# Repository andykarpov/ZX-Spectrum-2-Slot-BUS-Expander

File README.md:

# ZX-Spectrum-2Slot-BUS-Expander

Modified original version with Nemo Bus slot.

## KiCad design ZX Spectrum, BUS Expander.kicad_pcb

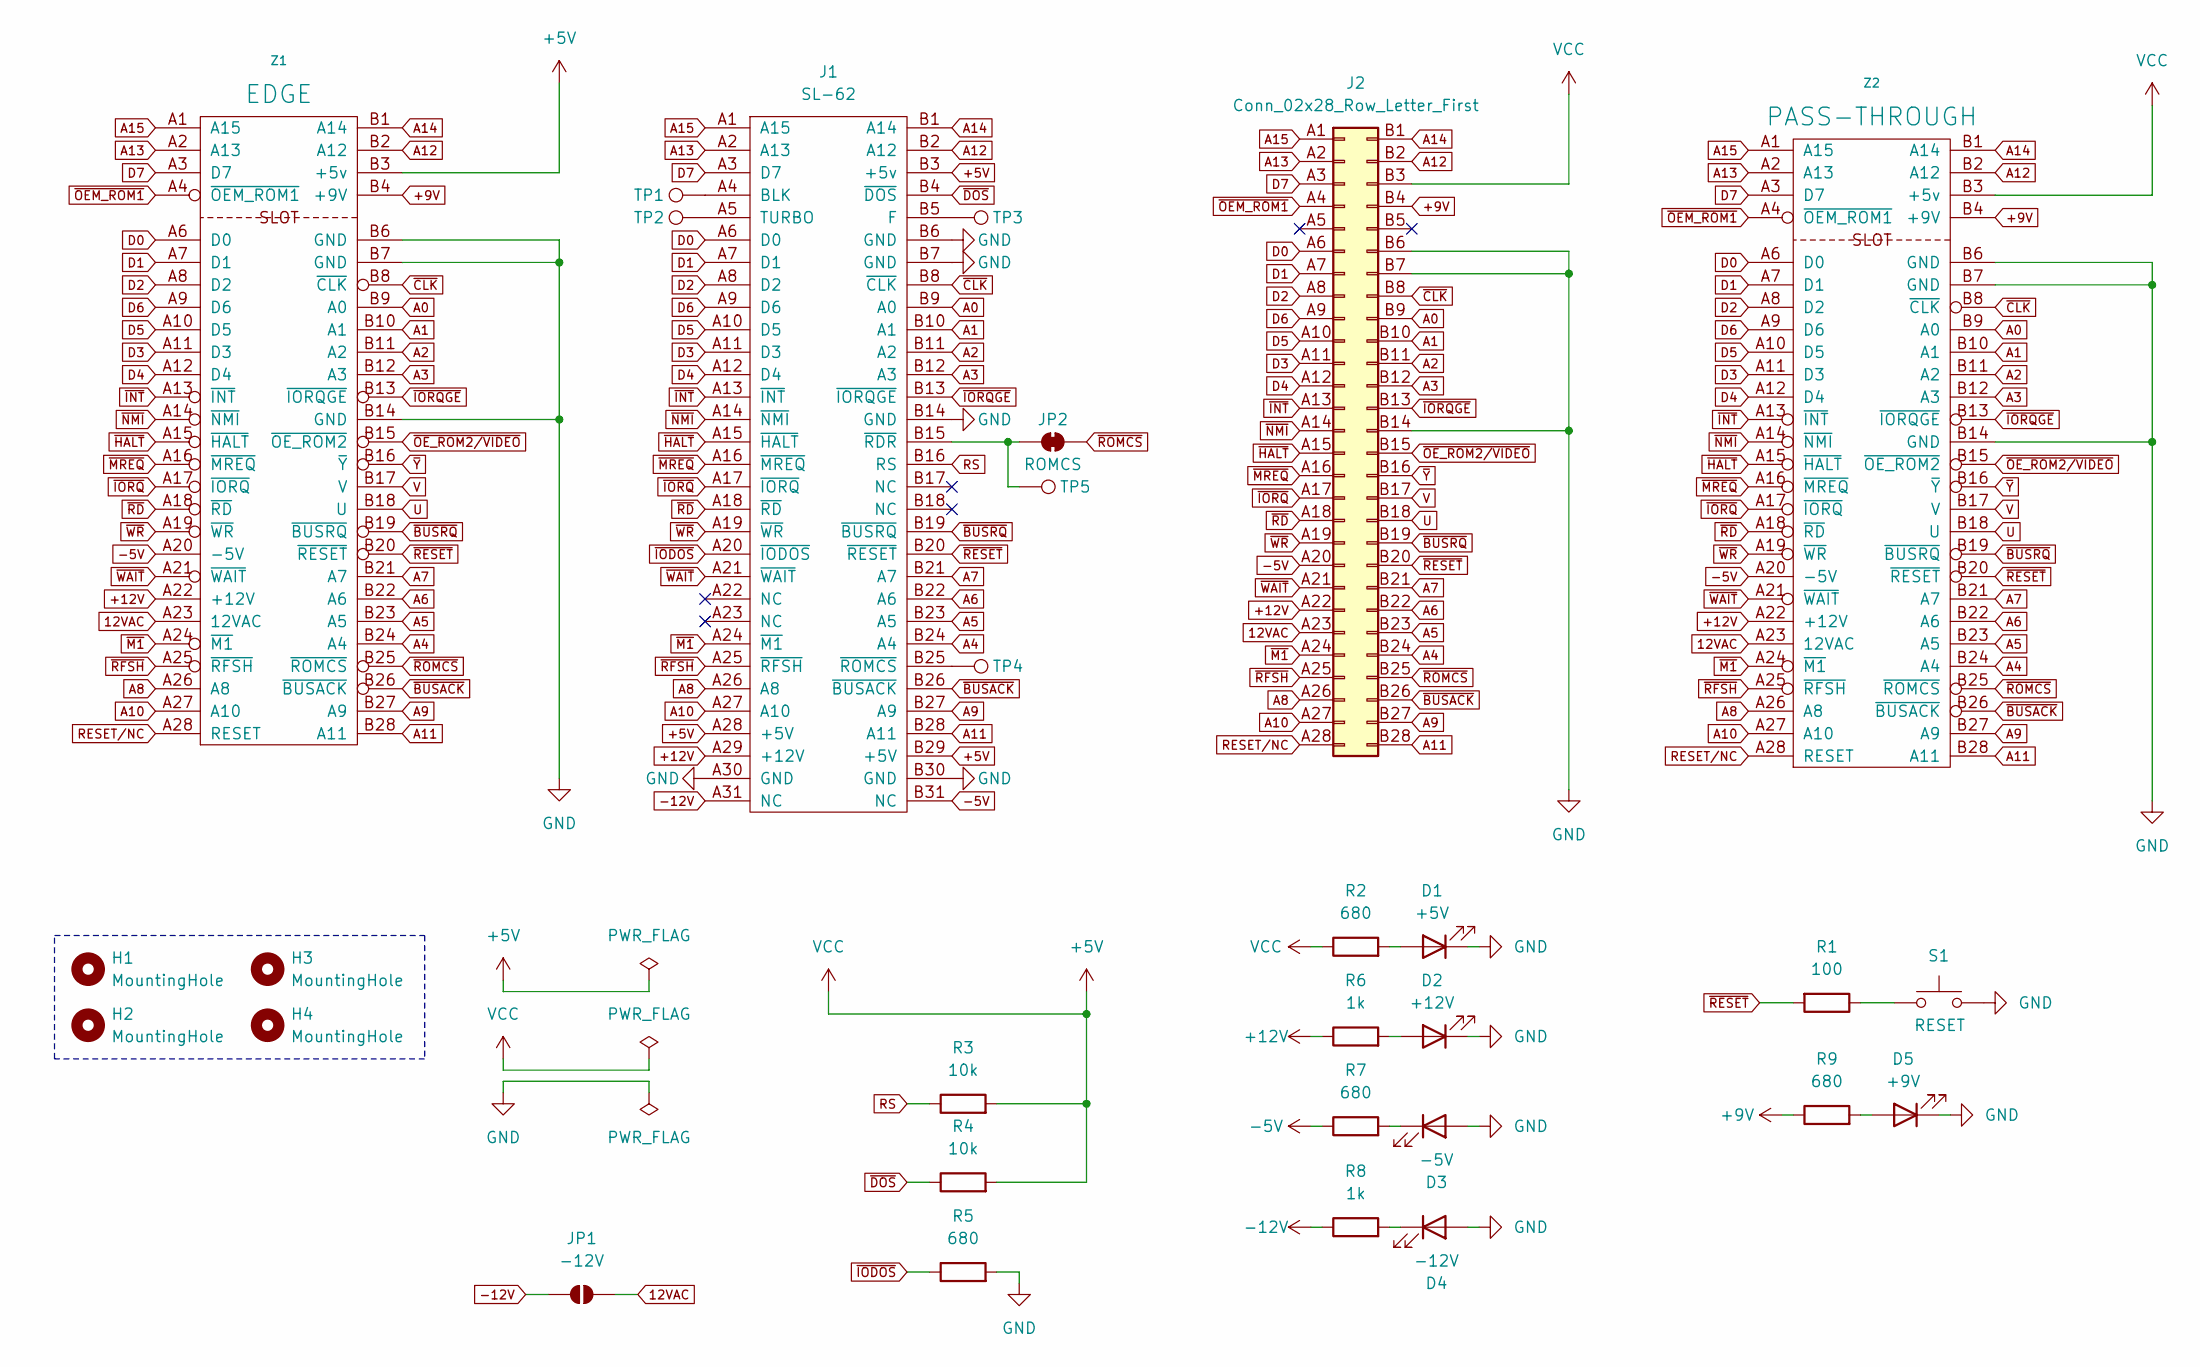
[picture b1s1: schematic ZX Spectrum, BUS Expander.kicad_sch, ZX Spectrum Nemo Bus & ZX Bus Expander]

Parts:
D1: +5V; LED_0805_2012Metric_Pad1.15x1.40mm_HandSolder
D2: +12V; LED_0805_2012Metric_Pad1.15x1.40mm_HandSolder
D3: -5V; LED_0805_2012Metric_Pad1.15x1.40mm_HandSolder
D4: -12V; LED_0805_2012Metric_Pad1.15x1.40mm_HandSolder
D5: +9V; LED_0805_2012Metric_Pad1.15x1.40mm_HandSolder
H1, H2, H3, H4: MountingHole; MountingHole_3.2mm_M3
J1: SL-62; NemoBus-SL62-inverted
J2: Conn_02x28_Row_Letter_First; ZX Bus Socket
JP1: -12V; SolderJumper-2_P1.3mm_Open_RoundedPad1.0x1.5mm
JP2: ROMCS; SolderJumper-2_P1.3mm_Bridged_RoundedPad1.0x1.5mm
R1: 100; R_0805_2012Metric_Pad1.20x1.40mm_HandSolder
R2, R5, R7, R9: 680; R_0805_2012Metric_Pad1.20x1.40mm_HandSolder
R3, R4: 10k; R_0805_2012Metric_Pad1.20x1.40mm_HandSolder
R6, R8: 1k; R_0805_2012Metric_Pad1.20x1.40mm_HandSolder
S1: RESET; SW_PUSH_6mm; Mouser Part Number 611-PTS526SM15SMTR2L
TP1, TP2, TP3, TP4, TP5: TestPoint; TestPoint_Pad_D2.0mm
Z1: EDGE; ZX Bus, Edge
Z2: PASS-THROUGH; ZX Bus, Edge Pass-T

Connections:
12VAC: J2.A23 (Pin_a23), JP1.2 (B), Z1.A23 (12VAC), Z2.A23 (12VAC)
+5V: J1.A28 (+5V), J1.B3 (+5v), J1.B29 (+5V), J2.B3 (Pin_b3), R2.1, R3.2, R4.2, Z1.B3 (+5v), Z2.B3 (+5v)
+9V: J2.B4 (Pin_b4), R9.1, Z1.B4 (+9V), Z2.B4 (+9V)
+12V: J1.A29 (+12V), J2.A22 (Pin_a22), R6.1, Z1.A22 (+12V), Z2.A22 (+12V)
-5V: J1.B31 (NC), J2.A20 (Pin_a20), R7.1, Z1.A20 (-5V), Z2.A20 (-5V)
-12V: J1.A31 (NC), JP1.1 (A), R8.1
A0: J1.B9 (A0), J2.B9 (Pin_b9), Z1.B9 (A0), Z2.B9 (A0)
A1: J1.B10 (A1), J2.B10 (Pin_b10), Z1.B10 (A1), Z2.B10 (A1)
A2: J1.B11 (A2), J2.B11 (Pin_b11), Z1.B11 (A2), Z2.B11 (A2)
A3: J1.B12 (A3), J2.B12 (Pin_b12), Z1.B12 (A3), Z2.B12 (A3)
A4: J1.B24 (A4), J2.B24 (Pin_b24), Z1.B24 (A4), Z2.B24 (A4)
A5: J1.B23 (A5), J2.B23 (Pin_b23), Z1.B23 (A5), Z2.B23 (A5)
A6: J1.B22 (A6), J2.B22 (Pin_b22), Z1.B22 (A6), Z2.B22 (A6)
A7: J1.B21 (A7), J2.B21 (Pin_b21), Z1.B21 (A7), Z2.B21 (A7)
A8: J1.A26 (A8), J2.A26 (Pin_a26), Z1.A26 (A8), Z2.A26 (A8)
A9: J1.B27 (A9), J2.B27 (Pin_b27), Z1.B27 (A9), Z2.B27 (A9)
A10: J1.A27 (A10), J2.A27 (Pin_a27), Z1.A27 (A10), Z2.A27 (A10)
A11: J1.B28 (A11), J2.B28 (Pin_b28), Z1.B28 (A11), Z2.B28 (A11)
A12: J1.B2 (A12), J2.B2 (Pin_b2), Z1.B2 (A12), Z2.B2 (A12)
A13: J1.A2 (A13), J2.A2 (Pin_a2), Z1.A2 (A13), Z2.A2 (A13)
A14: J1.B1 (A14), J2.B1 (Pin_b1), Z1.B1 (A14), Z2.B1 (A14)
A15: J1.A1 (A15), J2.A1 (Pin_a1), Z1.A1 (A15), Z2.A1 (A15)
D0: J1.A6 (D0), J2.A6 (Pin_a6), Z1.A6 (D0), Z2.A6 (D0)
D1: J1.A7 (D1), J2.A7 (Pin_a7), Z1.A7 (D1), Z2.A7 (D1)
D2: J1.A8 (D2), J2.A8 (Pin_a8), Z1.A8 (D2), Z2.A8 (D2)
D3: J1.A11 (D3), J2.A11 (Pin_a11), Z1.A11 (D3), Z2.A11 (D3)
D4: J1.A12 (D4), J2.A12 (Pin_a12), Z1.A12 (D4), Z2.A12 (D4)
D5: J1.A10 (D5), J2.A10 (Pin_a10), Z1.A10 (D5), Z2.A10 (D5)
D6: J1.A9 (D6), J2.A9 (Pin_a9), Z1.A9 (D6), Z2.A9 (D6)
D7: J1.A3 (D7), J2.A3 (Pin_a3), Z1.A3 (D7), Z2.A3 (D7)
GND: D1.1 (K), D2.1 (K), D3.2 (A), D4.2 (A), D5.1 (K), J1.A30 (GND), J1.B6 (GND), J1.B7 (GND), J1.B14 (GND), J1.B30 (GND), J2.B6 (Pin_b6), J2.B7 (Pin_b7), J2.B14 (Pin_b14), R5.2, S1.2, Z1.B6 (GND), Z1.B7 (GND), Z1.B14 (GND), Z2.B6 (GND), Z2.B7 (GND), Z2.B14 (GND)
unnamed: D1.2 (A), R2.2
unnamed: D2.2 (A), R6.2
unnamed: D3.1 (K), R7.2
unnamed: D4.1 (K), R8.2
unnamed: D5.2 (A), R9.2
unnamed: J1.A4 (BLK), TP1.1
unnamed: J1.B5 (F), TP3.1
unnamed: J1.A5 (TURBO), TP2.1
unnamed: J1.B15 (~RDR), JP2.1 (A), TP5.1
unnamed: J1.B25 (~ROMCS), TP4.1
unnamed: R1.1, S1.1
RESET/NC: J2.A28 (Pin_a28), Z1.A28 (RESET), Z2.A28 (RESET)
RS: J1.B16 (RS), R3.1
U: J2.B18 (Pin_b18), Z1.B18 (U), Z2.B18 (U)
V: J2.B17 (Pin_b17), Z1.B17 (V), Z2.B17 (V)
~BUSACK: J1.B26 (~BUSACK), J2.B26 (Pin_b26), Z1.B26 (~BUSACK), Z2.B26 (~BUSACK)
~BUSRQ: J1.B19 (~BUSRQ), J2.B19 (Pin_b19), Z1.B19 (~BUSRQ), Z2.B19 (~BUSRQ)
~CLK: J1.B8 (~CLK), J2.B8 (Pin_b8), Z1.B8 (~CLK), Z2.B8 (~CLK)
~DOS: J1.B4 (~DOS), R4.1
~HALT: J1.A15 (~HALT), J2.A15 (Pin_a15), Z1.A15 (~HALT), Z2.A15 (~HALT)
~INT: J1.A13 (~INT), J2.A13 (Pin_a13), Z1.A13 (~INT), Z2.A13 (~INT)
~IODOS: J1.A20 (~IODOS), R5.1
~IORQGE: J1.B13 (~IORQGE), J2.B13 (Pin_b13), Z1.B13 (~IORQGE), Z2.B13 (~IORQGE)
~IORQ: J1.A17 (~IORQ), J2.A17 (Pin_a17), Z1.A17 (~IORQ), Z2.A17 (~IORQ)
~M1: J1.A24 (~M1), J2.A24 (Pin_a24), Z1.A24 (~M1), Z2.A24 (~M1)
~MREQ: J1.A16 (~MREQ), J2.A16 (Pin_a16), Z1.A16 (~MREQ), Z2.A16 (~MREQ)
~NMI: J1.A14 (~NMI), J2.A14 (Pin_a14), Z1.A14 (~NMI), Z2.A14 (~NMI)
~OEM_ROM1: J2.A4 (Pin_a4), Z1.A4 (~OEM_ROM1), Z2.A4 (~OEM_ROM1)
~OE_ROM2/VIDEO: J2.B15 (Pin_b15), Z1.B15 (~OE_ROM2), Z2.B15 (~OE_ROM2)
~RD: J1.A18 (~RD), J2.A18 (Pin_a18), Z1.A18 (~RD), Z2.A18 (~RD)
~RESET: J1.B20 (~RESET), J2.B20 (Pin_b20), R1.2, Z1.B20 (~RESET), Z2.B20 (~RESET)
~RFSH: J1.A25 (~RFSH), J2.A25 (Pin_a25), Z1.A25 (~RFSH), Z2.A25 (~RFSH)
~ROMCS: J2.B25 (Pin_b25), JP2.2 (B), Z1.B25 (~ROMCS), Z2.B25 (~ROMCS)
~WAIT: J1.A21 (~WAIT), J2.A21 (Pin_a21), Z1.A21 (~WAIT), Z2.A21 (~WAIT)
~WR: J1.A19 (~WR), J2.A19 (Pin_a19), Z1.A19 (~WR), Z2.A19 (~WR)
~Y: J2.B16 (Pin_b16), Z1.B16 (~Y), Z2.B16 (~Y)

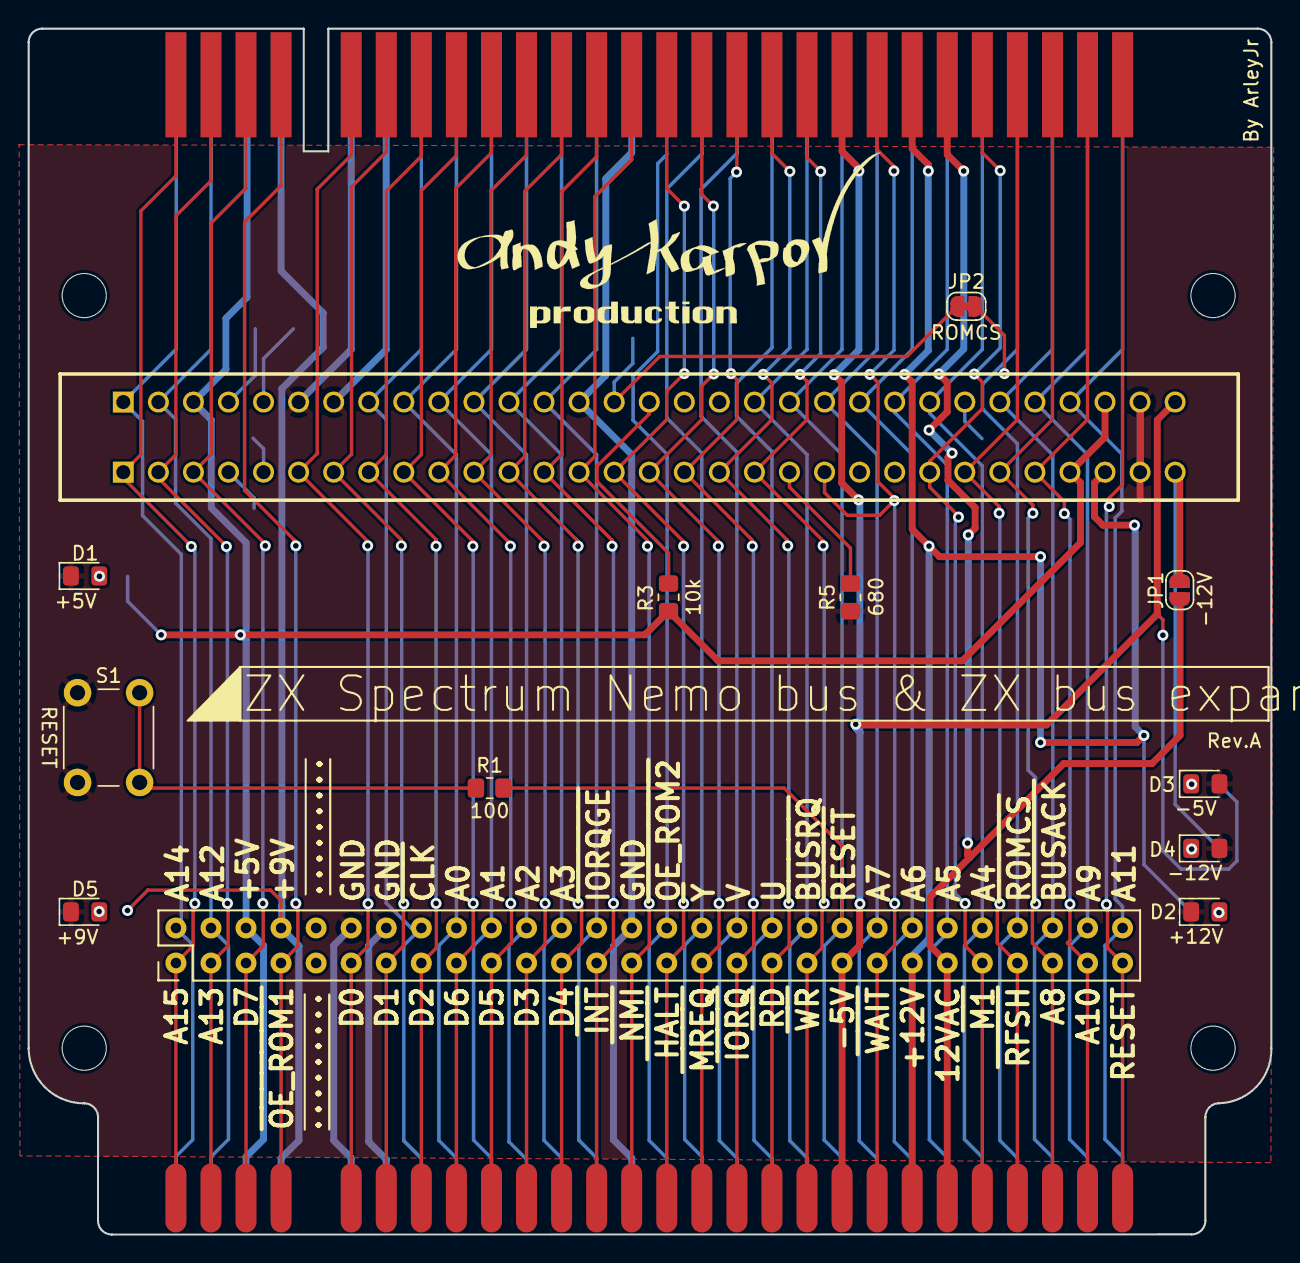
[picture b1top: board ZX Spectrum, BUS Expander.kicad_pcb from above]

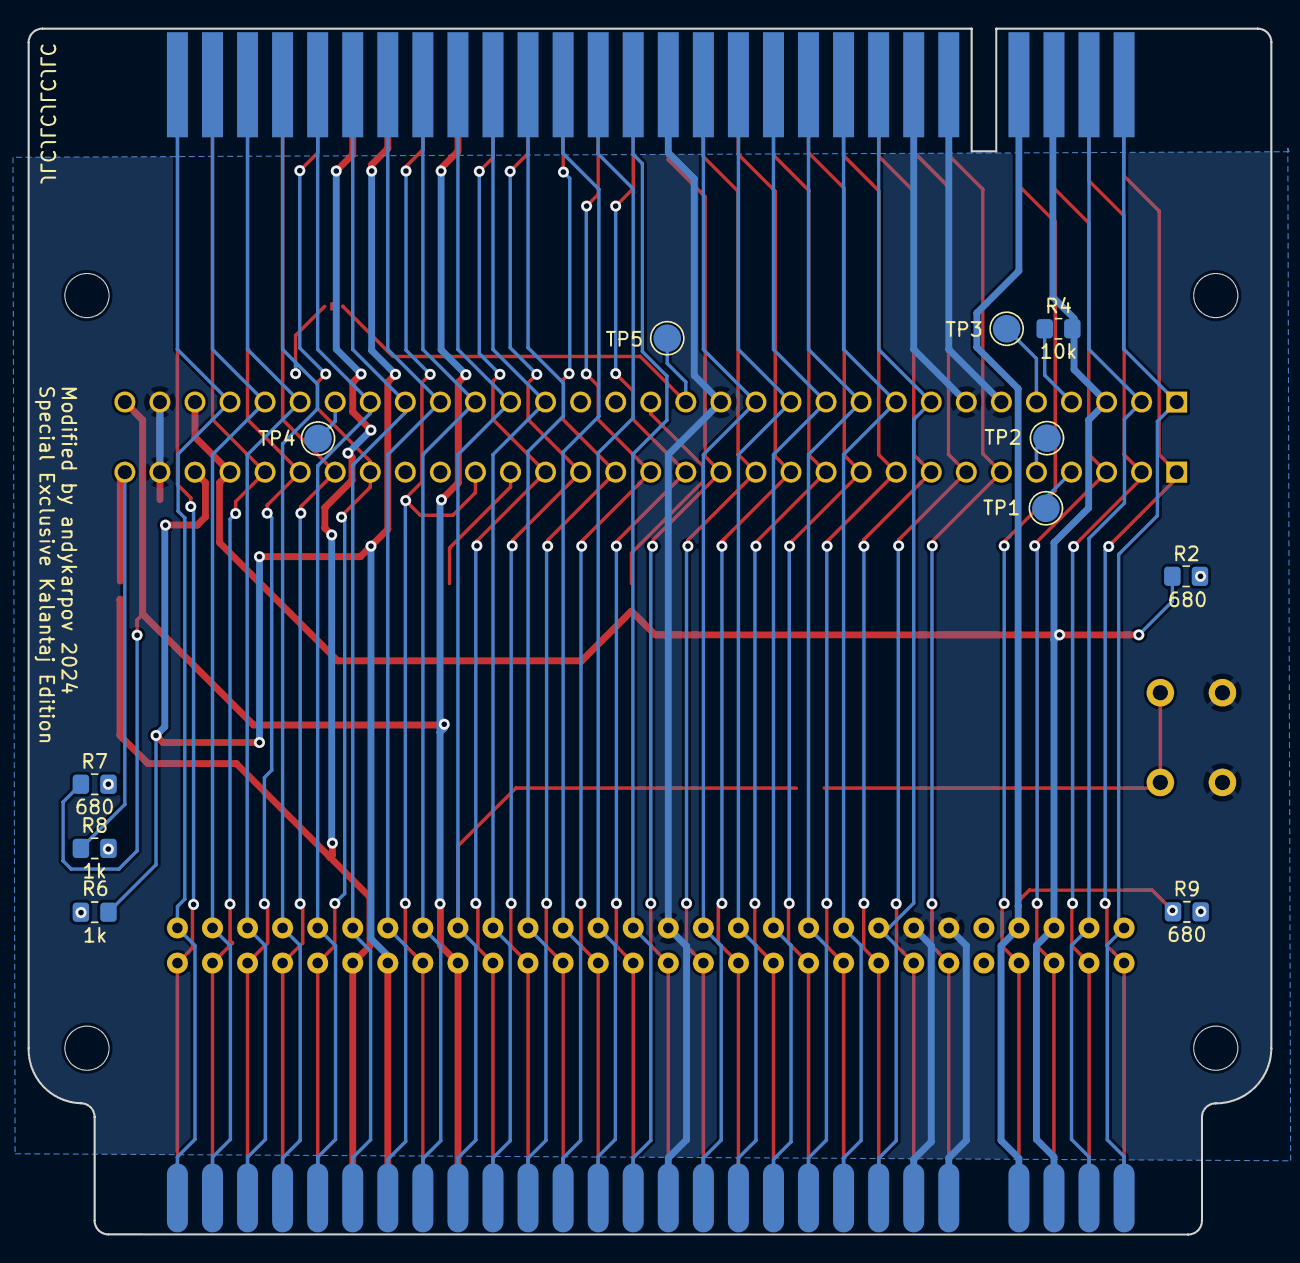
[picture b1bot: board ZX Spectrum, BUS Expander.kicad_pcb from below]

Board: 2 copper layers, 90.0 x 87.4 mm, 30 parts (11 on the bottom side), 67 nets.

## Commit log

2024-10-21 Added Nemo BUS
2024-10-21 Updated gerbers, added 1st pin on ZXbus
2024-10-21 removed outdated files
2024-10-21 Reorganized repo
2024-10-21 doc fix
2024-10-21 Updated silk, fixed edge pcb dimensions a bit
2024-10-21 Fixed Nemobus romcs signal
2024-10-22 Added more test points on nemobus slot
2024-10-22 Added more leds
